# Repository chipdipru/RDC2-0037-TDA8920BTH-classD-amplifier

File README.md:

<p></p>

<p>Модуль RDC2-0037 представляет собой высокопроизводительный усилитель мощности класса D. Усилитель построен на микросхеме TDA8920B. Это стереофонический аналоговый чип с цифровым усилителем, предназначенный для работы с 4-омными громкоговорителями мощностью до 110 Вт на канал.<br>RDC2-0037 сконфигурирован для работы с двумя каналами включенными по мостовой схеме (BTL).<br>На аналоговый вход усилителя можно подавать как несимметричный так и симметричный (дифференциальный) сигнал.<br>
 Встроенная система защиты отслеживает: перегрев, перегрузку и короткое замыкание выходов. При наличии одной из вышеперечисленных ошибок усилитель отключается, а после устранения ошибки восстанавливает работу.<br>Для обеспечения высококачественного высокоэффективного усиления звука требуется простой пассивный фильтр демодуляции цифрового сигнала. Модуль LCF.</p>
<h2>Технические характеристики</h2>
<p>Напряжение питания выходного каскада: ±12.5 ... ±30 В<br>Количество каналов: 2 x BTL<br>Сопротивление нагрузки: 3-8 Ом<br>Выходная мощность: BTL 110 Вт / 3 Ом 10% THD<br>Выходная мощность BTL 86 Вт / 4 Ом / 10% THD<br>Выходная мощность: PBTL 210 Вт / 6 Ом 10% THD<br>Выходная мощность: BTL 69 Вт / 4 Ом / 0,5% THD<br>Коэффициент нелинейных искажений:0.02%</p>
<p>Схема основной платы усилителя.</p>
<p></p>
<p>Подробную инструкцию по включению и конфигурации усилителя можно найти в разделе «Документы».</p>
<p>Это открытый проект! Лицензия, под которой он распространяется – <a href="https://creativecommons.org/licenses/by-sa/3.0/" class="link">Creative Commons - Attribution - Share Alike license</a>.</p>

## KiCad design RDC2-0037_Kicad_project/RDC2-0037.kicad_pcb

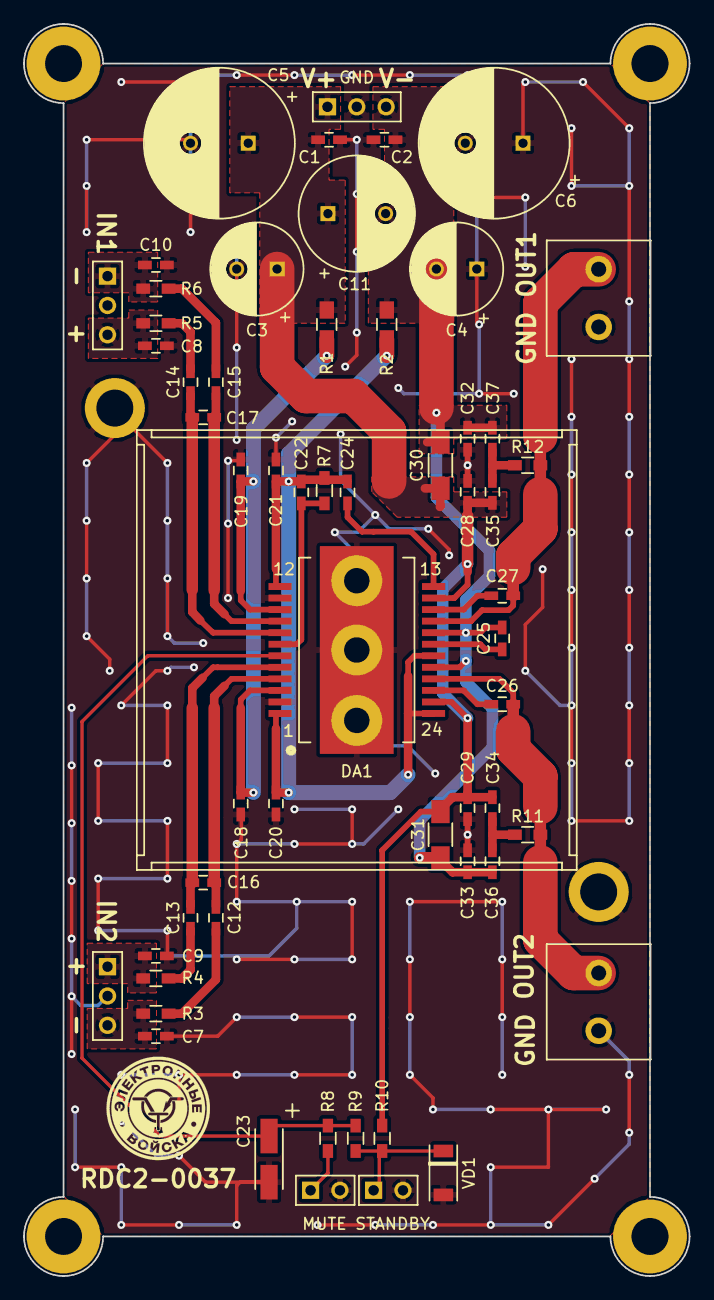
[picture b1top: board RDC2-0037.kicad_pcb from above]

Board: 2 copper layers, 57.7 x 108.5 mm, 62 parts (0 on the bottom side), 29 nets.

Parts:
C1, C2, C7, C8, C9, C10, C12, C13, C14, C15, C16, C17, C18, C19, C20, C21, C22, C24, C25, C26, C27, C28, C29, C32, C33, C34, C35, C36, C37: C; C_0603_HandSoldering
C3, C4: CP; C_Radial_D8_L11.5_P3.5
C5, C6: CP; C_Radial_D13_L21_P5
C11: CP; C_Radial_D10_L20_P5
C23: CP; TantalC_SizeA_EIA-3216_HandSoldering_mm
C30, C31: C; C_1206_HandSoldering
DA1: TDA8920; HSOP24
GND_HOLE: MountingHole_2.2mm_M2_Pad
GND_HOLE#2, GND_HOLE#3: MountingHole_2.2mm_M2_Pad
HeatSink: Heatsink_37x37mm_SpringFixation
R1, R2: R; C_0805_HandSoldering
R3, R4, R5, R6, R7, R8, R9, R10, R11, R12: R; R_0603_HandSoldering
VD1: ZENER; Diode_SOD-80
XP1, XP2, XP3: CONN_01X03; Pin_Header_Straight_1x03_mm
XP4, XP5: CONN_01X02; Pin_Header_Straight_1x02_mm
XS1, XS2: CONN_01X02; Clem_2Pos_P5

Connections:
GND: C1.2, C2.1, C3.2, C4.1, C5.2, C6.1, C7.2, C8.2, C9.2, C10.2, C18.2, C19.2, C20.2, C21.2, C23.2, C28.2, C29.2, C32.2, C33.2, DA1.2, DA1.11, DA1.25, GND_HOLE.1, GND_HOLE#2.1, GND_HOLE#3.1, HeatSink.1, VD1.2, XP1.2, XP2.2, XP3.2, XP4.2, XP5.2, XS1.2, XS2.2
unnamed: C7.1, R3.2, XP2.3
unnamed: C8.1, R5.2, XP3.3
unnamed: C9.1, R4.2, XP2.1
unnamed: C10.1, R6.2, XP3.1
unnamed: C12.1, C16.1, DA1.4
unnamed: C12.2, R3.1
unnamed: C13.1, C16.2, DA1.5
unnamed: C13.2, R4.1
unnamed: C14.1, C17.1, DA1.8
unnamed: C14.2, R5.1
unnamed: C15.1, C17.2, DA1.9
unnamed: C15.2, R6.1
unnamed: C22.1, DA1.7, R7.1
unnamed: C23.1, DA1.6, R8.2, R9.2
unnamed: C24.1, DA1.13
unnamed: C25.1, DA1.18
unnamed: C26.1, DA1.22
unnamed: C26.2, DA1.21, R11.1, XS1.1
unnamed: C27.1, DA1.16, R12.1, XS2.1
unnamed: C27.2, DA1.15
unnamed: C34.1, C36.1, R11.2
unnamed: C35.1, C37.1, R12.2
unnamed: R8.1, XP4.1
unnamed: R9.1, R10.1, VD1.1, XP5.1
VA+: C18.1, C19.1, DA1.3, DA1.10, R1.2
VA-: C20.1, C21.1, C22.2, C24.2, DA1.1, DA1.12, DA1.19, DA1.24, R2.2, R7.2
VP+: C1.1, C3.1, C5.1, C11.1, C28.1, C29.1, C30.1, C31.1, C34.2, C35.2, DA1.14, DA1.23, R1.1, R10.2, XP1.1
VP-: C2.2, C4.2, C6.2, C11.2, C25.2, C30.2, C31.2, C32.1, C33.1, C36.2, C37.2, DA1.17, DA1.20, R2.1, XP1.3

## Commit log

2018-09-27 KiCad project
